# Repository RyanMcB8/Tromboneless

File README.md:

# Tromboneless

<a href="https://github.com/RyanMcB8/Tromboneless/releases" alt="Latest release">
        < /></a>

</p>

This GitHub repository contains the hardware and firmware for Tromboneless - an open source device capable of measuring oral input to synthesise the output of a brass trombone using a Raspberry Pi 5, implementing MIDI protocol. 

Tromboneless also contains its own internal synth, with custom control via the Tromboneless App!

Please refer to our [wiki](https://github.com/RyanMcB8/Tromboneless/wiki) for more information relating to components, program sequence and state diagrams for MIDI protocol implementation.

## Table of Contents
- [Set-Up Guide](#set-up-guide)
- [Dependencies](#dependencies)
- [Bill of Materials](#bill-of-materials)
- [Social Media](#social-media)
- [Documentation](#documentation)
- [Authors & Contributions](#authors-and-contributions)

## Set-Up Guide

### Installing PiOS on Raspberry Pi 5

1.  For set-up guidance for PiOS, please follow [this guide](https://www.raspberrypi.com/documentation/computers/getting-started.html#installing-the-operating-system) <br>
   <br>

### Cloning Tromboneless

2. After installing PiOS on the Raspberry Pi 5, 

   In the terminal or command line, run:

    ```
      git clone --recursive https://github.com/RyanMcB8/Tromboneless.git
   ```

**Note : Make sure git is installed on the Raspberry Pi 5.**

### Installing Libraries

3. Tromboneless software makes use of third-party libraries which are integral to the running of Tromboneless. 

| Library | Purpose |
|---|---|
| [JUCE](https://juce.com/) | UI framework |
| [RtMidi](https://github.com/thestk/rtmidi) | Handles the communication from USB Midi devices. |
| [RPi_ads1115](https://github.com/berndporr/rpi_ads1115/tree/f434fb9c197e0314af69fa5ee3839f8655fad72c) | [Bernd Porr ADC Library](https://github.com/berndporr/rpi_ads1115) used in pressure sensing. | 

### Installing Dependencies

4. The Tromboneless App uses the [JUCE](https://juce.com/) framework for all UI widgets, and uses the following dependencies:

| Library | Purpose | License |
|---|---|---|
| [JUCE](https://juce.com/) | UI framework | AGPLv3 / Commercial |
| RTMidi | MIDI I/O | MIT |
| libgpiod-dev | GPIO pin interaction (Raspberry Pi) | LGPLv2.1+ |
| pkg-config | Library detection at compile time | GPLv2 |
| libgtk-3-dev | App backend | LGPLv2.1+ |
| libwebkit2gtk-4.1-dev | Cross-platform support | LGPLv2.1+ |
| libcurl4-openssl-dev | HTTP/network support | MIT/curl |
| ALSA | Audio output for the internal synth | LGPLv2.1+ |
| freetype2 | Font rendering | FTL / GPLv2 |
| build-essential | Building the project | Various (GPL) |
| cmake | Building the project | BSD 3-Clause |
| libssl-dev | JUCE dependency | Apache 2.0 |

A **bash script** was created for a **single-command install** and build of all dependencies used in Tromboneless:

```
./makeTromboneless.sh
```

Running this in the ```Tromboneless``` directory will install all necessary dependencies and then build the Tromboneless project. 

Once the project has been built, there will be a prompt to run the script instantly.

Alternatively, the dependencies may be installed independently using the lines below in your terminal.

```
sudo apt install libgpiod-dev pkg-config libgtk-3-dev libwebkit2gtk-4.1-dev libcurl4-openssl-dev build-essential cmake-build libssl-dev
```

**Note: The first build of the software may require more than five minutes to complete. This is expected behaviour and will not affect subsequent runs.**

## Bill of Materials

To build the Tromboneless hardware, the following materials are required:

### Computation

|   | Quantity | Cost (£) |
|------------------|----------|----------|
| Raspberry Pi 5   | 1        |     ~58.98|
| Active Cooler for Raspberry Pi 5 (recommended)  | 1        |     4.80|

### Sensors

| Sensors                                                        | Quantity | Cost (£) |
|----------------------------------------------------------------|----------|----------|
| [VL53L1X](https://shop.pimoroni.com/products/vl53l1x-breakout?variant=12628497236051) Time of Flight (ToF) Sensor Breakout                   | 1        |  16.50   |
| [CAP1188](https://thepihut.com/products/adafruit-cap1188-8-key-capacitive-touch-sensor-breakout-i2c-or-spi) 8-Key Capacitive Touch Sensor Breakout                          | 1        |  7.70    |
| [ADS1115](https://shop.pimoroni.com/products/adafruit-ads1115-16-bit-adc-4-channel-with-programmable-gain-amplifier?variant=370782375) 16-bit ADC Breakout                                            | 1        |  14.70    |

Total Sensor Cost: £38.90

### Additional Components

| Additional Components                                          | Quantity | 
|----------------------------------------------------------------|----------|
| 1.0 M Ohm Resistor                                               | 1        |    
| 300.0 Ohm Resistor                                               | 1        |   
| USB MIDI Cable                                                 | 1        |    
| Infrared LED                                                   | 1        |    
| Photodiode                                                     | 1        |
| USB Sound Card                                                     | 1        |

### Hardware Assembly

Once all materials have been acquired, we can now begin to assemble the Tromboneless hardware.

1. Click [here](Documentation/Hardware/Mouthpiece_Construction_G.md) and follow step-by-step assembly instructions to create the mouthpiece used in the Tromboneless hardware.

2. Using the components outlined [above](#bill-of-materials), connect  the circuit andintegrate with the mouthpiece and pin headers on the Pi exactly as shown:

### Hardware-Software Integration

3. To verify sensors, install ```i2c-tools``` to confirm that sensors are being correctly recognised by the Raspberry Pi 5 i2c bus.

 ```
 sudo apt install i2c-tools
 i2cdetect -y 1
 ```

  Three devices should appear, and this confirms the correct configuration.
  
  If any do not show, check wiring and use [i2c-tools](https://www.kali.org/tools/i2c-tools/) for troubleshooting.

   4. Connect USB output of Raspberry Pi 5 to an external MIDI-compatible synthesizer, or use a USB sound card to output audio directly using the internal   synthesizer. 

5. Finally, in ```Tromboneless``` directory, run:

   ```
   ./makeTromboneless.sh
   ```
   This runs the dedicated bash [script](#installing-dependencies), and a prompt will appear to begin the program. 

   6. Use mouthpiece to trigger and change notes and distance sensor to bend notes with 7 semi-tone range. The app can be used to modify these parameters in real time.

## Social Media

 - **#1 Post** on [r/Trombone](https://www.reddit.com/r/Trombone/) (17-02-26) <br>

 - **#2 Post** on [r/Trombone](https://www.reddit.com/r/Trombone/comments/1s8ptlm/tromboneless_update/) (31-03-26) <br>

 - **28.6k+ total views** across [r/Embedded](https://www.reddit.com/r/embedded/comments/1sgra2m/tromboneless_update/), [r/Trombone](https://www.reddit.com/r/Trombone/comments/1r6bswo/tromboneless/) and [r/linuxaudio](https://www.reddit.com/r/linuxaudio/comments/1skgn6u/the_tromboneless/).

The social media strategy was devised to reach audiences already likely to be interested in the project, with the initial announcement designed to spark debate and create a hype around the project, this initial post gained over 10k views and was the #1 post on r/Trombone that day.

 Using this model, three main forums targeted were:
   - [r/embedded](https://www.reddit.com/r/embedded/)
   - [r/linuxaudio](https://www.reddit.com/r/linuxaudio/)
   - [r/trombone](https://www.reddit.com/r/Trombone/)

 A comparative analysis of early Instagram and Reddit analytics led us to prioritise Reddit as the main communication channel. The forum-based structure proved better suited to fostering direct engagement with the target audience. 

 As mentioned, our posts collectively received over 28.6lk views and frequent interaction across the different targeted channels throughout the project, as can be seen [here](https://www.reddit.com/user/Forward_Vehicle4096/). 
 
Follow our pages linked below for Tromboneless demonstrations, updates and new development! <br>

[Reddit](https://www.reddit.com/user/Forward_Vehicle4096/)<br>
[Instagram](https://www.instagram.com/tromboneless.tech/)<br>

and check out our **Tromboneless v1.0.0 release video**: 

**Click the image below!**

## Documentation

For full documentation of the Tromboneless software, refer to the [Documentation](https://github.com/RyanMcB8/Tromboneless/tree/main/Documentation) folder, which contains both LaTeX and HTML versions.

### Datasheets

All datasheets for components used can be located [here](Documentation/Hardware/datasheets).

## Authors and Contributions

- **Ben Allen** - Driver for the CAP1188 capacitive sensor, sensor data processing, Arduino prototyping, hardware design and construction, PCB design, and Tromboneless player.

- **Aidan McIntosh** - High-level event-handling, musical coordination, external MIDI integration

- **Ryan McBride** - Internal synthesiser and envelope design, creation of the App side for calibration and changing of parameters in real-time and all associated test scripts. Developed the CMakeLists to create libraries to reduce repetitive compilations.

- **Kerr McLaren** - ToF 'Slide' sensor integration and I2C communication set-up. 

- **Ciaran Rogers** - ADS1115 Pressure-sensor wrapper, initial CMake and JUCE App bring-up, audioRender integration, Documentation, Social Media/PR Strategy.

<!-- ### ADS1115 

- ADS1115 library adopted from [Bernd Porr](https://github.com/berndporr), which can be sourced [here](https://github.com/berndporr/rpi_ads1115). -->

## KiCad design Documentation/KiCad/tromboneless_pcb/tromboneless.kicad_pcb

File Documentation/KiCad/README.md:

## KiCAD PCB
The KiCAD schematic for the PCB can be found here. This PCB was made to interface between the Raspberry Pi 5
and the sensors.

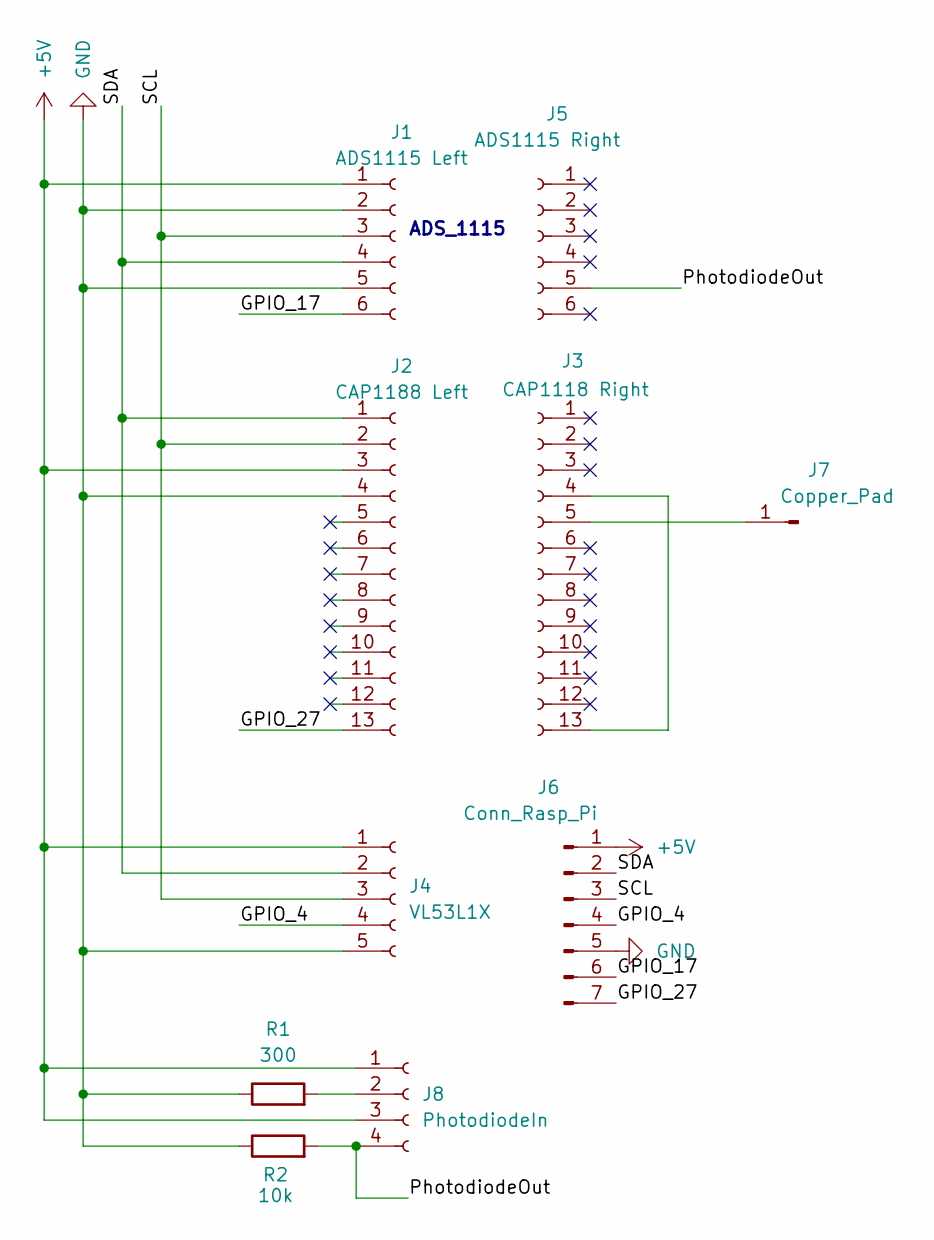
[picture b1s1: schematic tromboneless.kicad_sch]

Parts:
J1: ADS1115 Left; PinSocket_1x06_P2.54mm_Vertical
J2: CAP1188 Left; PinSocket_1x13_P2.54mm_Vertical
J3: CAP1118 Right; PinSocket_1x13_P2.54mm_Vertical
J4: VL53L1X; PinHeader_1x05_P2.54mm_Vertical
J5: ADS1115 Right; PinSocket_1x06_P2.54mm_Vertical
J6: Conn_Rasp_Pi; PinHeader_1x07_P2.54mm_Vertical
J7: Copper_Pad; PinHeader_1x01_P2.54mm_Vertical
J8: PhotodiodeIn; Molex_KK-254_AE-6410-04A_1x04_P2.54mm_Vertical
R1: 300; R_Axial_DIN0207_L6.3mm_D2.5mm_P7.62mm_Horizontal
R2: 10k; R_Axial_DIN0207_L6.3mm_D2.5mm_P7.62mm_Horizontal

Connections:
+5V: J1.1, J2.3, J4.1, J6.1, J8.1, J8.3
/GPIO_4: J4.4, J6.4
/GPIO_17: J1.6, J6.6
/GPIO_27: J2.13, J6.7
/PhotodiodeOut: J5.5, J8.4, R2.2
/SCL: J1.3, J2.2, J4.3, J6.3
/SDA: J1.4, J2.1, J4.2, J6.2
GND: J1.2, J1.5, J2.4, J4.5, J6.5, R1.1, R2.1
unnamed: J3.5, J7.1
unnamed: J3.4, J3.13
unnamed: J8.2, R1.2

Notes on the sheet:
ADS_1115

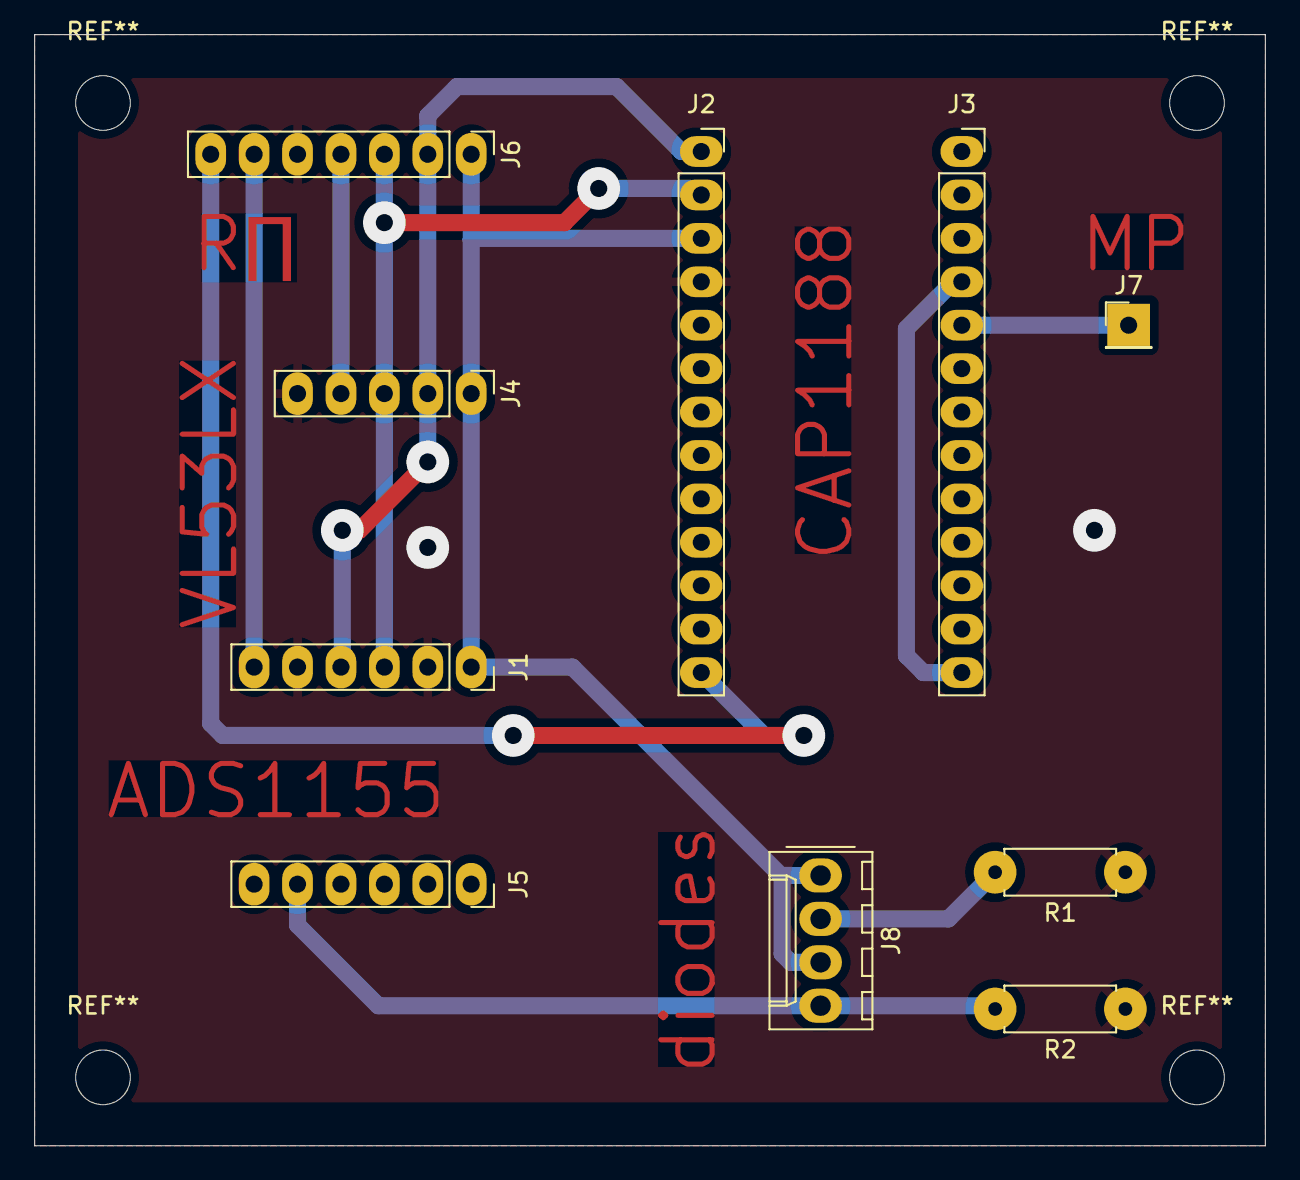
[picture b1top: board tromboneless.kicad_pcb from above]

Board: 2 copper layers, 72.0 x 65.0 mm, 10 parts (0 on the bottom side), 11 nets.

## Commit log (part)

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2026-02-11 Enhance SSH steps in README with detailed commands
    Added detailed steps for generating SSH keys and connecting.
2026-02-11 Update SSH instructions in README
    Clarify SSH instructions for different network scenarios.
2026-02-11 Update SSH instructions and recommend VSCode usage
    Added recommendation to use VSCode for remote access.
2026-02-11 Correcting command
2026-02-12 testing commit
2026-02-13 Revert "Merge branch 'main' of https://github.com/RyanMcB8/Tromboneless"
    This reverts commit 776ab87943a5381b56cdaa9fac60005a45873552, reversing
    changes made to 79393dd4710ccccc76c77f0416e2ecc512f7e514.
    Reverting
2026-02-13 Revert "Reapply "Merge branch 'main' of https://github.com/RyanMcB8/Tromboneless""
    This reverts commit 7531543949623b642fed375950a2cbf74c5d32a2.
    Revert
2026-02-18 Initial commit.
2026-02-25 Update issue templates
2026-03-03 Initial JUCE App Push
2026-03-03 Creating a new branch dedicated to working on app.
2026-03-04 Update README with wiki link for MIDI implementation
    Added a link to the wiki for component and diagram details.
2026-03-04 Fixed incorrect comments
2026-03-04 built preliminary i2c bus class
2026-03-04 Correcting layout
2026-03-04 Ignoring .vscode file
2026-03-05 Add VL53L1X ToF Sensor API
2026-03-06 adding more comments
2026-03-10 The basic UX window appears now.
2026-03-11 Created a notes file to explain how the app is programmed. This code has capabilities to interact with the core functionality.
2026-03-16 Created 2 linear sliders for setting the range for calibration of the distance sensor.
2026-03-16 Add an additional slider for adjusting pressure influence.
2026-03-18 Tidying up code and updating CMakeLists. Cleaning up GitHub merge issues with ciaran_branch.
2026-03-20 Added support for base class with slider and labels attached.
2026-03-20 Added functionality for the equalizer to change parameters.
2026-03-21 Initial synth classes and CMake for the main code.
2026-03-21 Adding decaying functionality to harmonics when they have been released.
2026-03-22 Changing the h files to be hpp.
2026-03-22 Added a Trombone slider as the slider for calibrating the distances.
2026-03-23 Start MidiCoordinator class
2026-03-24 Working on Midicoordinator class
2026-03-24 tidying up
2026-03-24 Initial VL53L1X integration with working I2C communication
2026-03-25 Added a feature to enable and disable the synth.
2026-03-25 Add empty methods for Midicoordinator
2026-03-25 Add method for Midi expression change
2026-03-25 Completed methods in MidiCoordinator
2026-03-25 Add VL53L1X ToF sensor driver with GPIO interrupt and callback-based data handling
2026-03-25 Add script to main to test midi pipeline
2026-03-25 Added a cmake to the main page to build all. Broke the pressure calibration slider.
2026-03-26 Add ADS1115rpi drivers
2026-03-26 Added ads drivers to test code
2026-03-27 Adding inheritance graphs to doxygen.
2026-03-27 Recompiled doxygen.
2026-03-27 Working on scaling logic
2026-03-30 Pressure calibration sliders working.
2026-03-31 UX basically complete. Just needs comments added.
2026-04-01 Added all the necessary comments to the widgets header file and updated doxygen.
2026-04-01 Stop tracking old VSCode settings
2026-04-02 Fix scaling
2026-04-02 Testing main using input handler
2026-04-02 Update gitignore
2026-04-02 Match new and old cmakelists
2026-04-02 personal notes added
2026-04-02 2nd attempt at getting the image to render.
2026-04-02 Adding more comments to the header files within the App.
2026-04-03 Started to add test scripts and updated readme.
2026-04-03 Setting up main loop for test.
2026-04-03 Rearranging the attack and decay functions.
2026-04-03 Starting testing of internal synth with audio output
2026-04-03 Created cmake for test and debugged
2026-04-03 Added the inital test script for the synth.
2026-04-03 Tests working now
2026-04-04 Changed synth_audio_test to output the raw data of teh amplitude.
2026-04-04 Ongoing testing of synth/audio integration
2026-04-06 Added missing breaks in switch statement and possible fix to oscillator logic
2026-04-07 Adding a note to the synth.hpp file.
2026-04-07 Adding rtmidi as submodule
2026-04-07 Move midi test to test folder
2026-04-07 Fix headers and test makelist
2026-04-07 Removing old MIDI folders.
2026-04-08 Fix external bend test logic
2026-04-08 added st ultra lite external driver api
2026-04-09 Adding the new envelope script. This has not been implemented or tested yet.
2026-04-09 Adding MIDI interface to the tromboneSynth.
2026-04-09 Starting to add more setters and getters to the custom styles files.
2026-04-10 Added setters and getters within the Panels files.
2026-04-10 Fixed octaves with harmonics logic
2026-04-10 Adding a startEnvelope function to the envelope files.
2026-04-10 Adding functionality for the RtMidi library to work as a submodule instead of included file.
2026-04-10 Added pitch bend feature to the tromboneSynth.
2026-04-10 Changing direct defintions to private variables to using setters and getters.
2026-04-10 Adding the setters/getters for the DualRotarySlider class but they have not been documented/commented on yet.
2026-04-11 All setter/getter functions have been created for the App variables.
2026-04-11 Fixed float divisions that were casting to integers
2026-04-11 Specified std::abs as c-style abs was casting to integer
2026-04-11 implemented platfrom specific i2c into external driver as per supplier instructions
2026-04-11 Small changes for clarity
2026-04-12 Modified the CMake to add the App library and enable tests.
2026-04-12 Changed the type of the embouchure option in the shared struct.
2026-04-12 Working version of CAP1188 drivers & test program
2026-04-12 Fixes to integer divisions and state change
2026-04-12 Fix logic for generating harmonics and inconsistent units
2026-04-12 Altered MIDI mapping to conform to standard (C4 = 60)
2026-04-12 Reconfigured synth to work in terms of phase rather than time
2026-04-12 ultra lite st driver for tof_sensor implemented
2026-04-13 amendements to lambda and to Cmakelists
2026-04-13 Improved functionality of CAP1188
2026-04-13 Fixed some errors within the app documentation.
2026-04-13 Change name of write/readblock to write/readblock16
2026-04-13 Changing the CMake order to allow for the shared library to be referenced by both the App and Core sides. Still need to modify the `include` calls to reference a library rather than uncompiled cpp co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
2026-04-13 Updating the doxygen config file to ignore the library used for the LiDAR sensor.
2026-04-13 Changing the shared parameters to be referenced as a library within the App and Core files.
2026-04-14 Removing example code from the STSW module.
2026-04-14 Touch release detection enabled
2026-04-14 Fix clearing cap_sensor interrupt
2026-04-15 Changing the CMake to build JUCE
2026-04-15 Beginning integration of midi coordinator and internal synth
2026-04-15 amendments to Cmakelists
2026-04-15 Changes for type safety and starting handler functions for internal synth MIDI functions
2026-04-16 Additional README update.
2026-04-16 audioRender Class Implementation.
2026-04-16 update with audio render
2026-04-16 Moving the shared directory outside of app so it may be used without needing to install the app folder.
2026-04-16 Implemented wrapper for ADS1115 library. Updated CMakeLists and removed unneccessary ADS1115 files.
2026-04-16 Fixed the issues in the App tests.
2026-04-16 Add rpi_ads1115 submodule
2026-04-16 doxygen commetns added to tof_sensor.hpp and updated comments in the .cpp
2026-04-16 Updating README and CirKit diagram.
2026-04-16 Adding the TrombonelessCore CmakeLists back
2026-04-16 Moved the test lidar script into the test directory.
2026-04-17 Adding the Core CMakeList to be functional.
2026-04-17 fixes to internal midi synth integration
2026-04-17 Added the unit tests for the envelope.
2026-04-17 Changing the way core is structured to allow for shared files.
2026-04-17 First working integration of all inputs, controlling the internal synth with MIDI coordinator, and rendering sound in realtime
2026-04-17 Added header for high-pass filter class
2026-04-17 Working automatic detection of external/internal synth
2026-04-17 Updated to latest submodule versions
2026-04-18 Adapting test script to work with encapsulated pitchmapping class
2026-04-18 Revert "Added header for high-pass filter class"
    This reverts commit 8ee5cd5e117680f79bcdf553cc3fb23f386bc801.
2026-04-18 Add initialisation error messages
2026-04-18 Optimise synth render path for realtime performance
    - Cache harmonic weights to avoid recomputation per sample
    - Cache pitch-dependent phase increment (update on note/bend change only)
    - Replace per-harmonic cos(n·phase) with recurrence (1 trig call per sample)
    - Remove redundant per-sample normalisation work
    - Reduce CPU load in audio thread to support lower latency
2026-04-18 Adding functionality to control the trombone max/min slide limits and transposition range via the app
2026-04-18 Refined amplitude mapper
2026-04-18 Added more dependencies to the list and my contributions.
2026-04-18 Added hysteresis behaviour to embouchure pitch mapping
2026-04-18 Started to implement a wrapper of main.cpp in core based off what Aidan and Ben Allen created.
2026-04-18 ignoring generated doxygen files
2026-04-18 Updated main to use the wrapper.
2026-04-18 Move includes to main header
2026-04-18 Refactor EventHandler to own event queue and provide blocking. Remove need for external queue management in main
2026-04-18 Added support for the pdf to be created using doyxgen.
2026-04-18 Stopped tracking the html and latex files.
2026-04-18 Latest documentation.
2026-04-18 Ignoring the .clangd file.
2026-04-19 Referencede the wrong directory when deleting the html and latex sub directories.
2026-04-19 App and core are built together now. Need to test if app works with core next by having the setters used.
2026-04-19 Makelist modified to not include main twice. Empty high level controller class created
2026-04-19 Adjusted CoreWrapper to account for new encapsulation of EventHandler
2026-04-19 Added new dependencies
2026-04-19 Removing the libgpiod submodule from the CMakeList and added a line in Cmake to ignore RtMidid warnings for null ptr.
2026-04-19 Trying to migrate to reduce the size of the juce library.
2026-04-19 Deleted duplicate code
2026-04-19 Matched test code to newly encapsulated eventhandler
2026-04-19 Fix switch block and bend logic
2026-04-19 Major changes to the CoreWrapper to allow for unit tests to run when there is no peripheral connected.
2026-04-19 Still running into hardware being built into the system.
2026-04-20 Tests can now compile, need to test if this affected the normal flow of the main code.
2026-04-20 Changed diagram from pdf to png so it can load in ReadMe.
2026-04-20 Changed pressure threshold weighting logic in widget, and renamed amplitudemapper method accordingly
2026-04-20 Update CMakeLists.txt
    Added the Core executable
2026-04-20 More fixes to makelists, added conditional to build without tests
2026-04-20 Update README.md
    Changed dependencies list.
2026-04-20 Restored missing lines
2026-04-20 Adjusted Barometer
2026-04-20 Added CirKit diagram with white background
2026-04-20 Update dox.sh to also installk dependencies
2026-04-20 Proper commenting in place
2026-04-20 Add deleteme file to Hardware images directory
2026-04-20 Commenting
2026-04-20 Added images to mpiece construct guide
2026-04-20 Finished mouthpiece construction guide
2026-04-20 Trying to make the build system faster.
2026-04-20 Add .gitignore for KiCad documentation files
2026-04-20 Unit test for MIDI Coordinator
2026-04-20 Added project folder
2026-04-20 Add README for KiCAD PCB documentation
2026-04-20 embouchure tuning
2026-04-20 Rename Screenshot 2026-04-20 at 19.23.52.png to pcb_drawing.png
2026-04-20 Center align PCB drawing in README
2026-04-20 Updated the libraries and dependencies
2026-04-20 Aidan contributions
2026-04-20 Added personal contribution
2026-04-20 Setting thread limit to 2.
2026-04-20 ReadMe with video integration.
2026-04-20 Moved App unit tests to be within the same test script.
2026-04-20 More ReadMe
2026-04-20 Final Documentation.
2026-04-20 ReadMe Push.
